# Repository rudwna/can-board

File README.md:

# MCP2515 + MCP2551 CAN development board

This board is for CAN bus development using MCP2515 CAN controller and MCP2551 CAN transceiver.
Created after experiences odd behaviors when using breadboard for development ([just like this](http://www.microchip.com/forums/m704332.aspx))

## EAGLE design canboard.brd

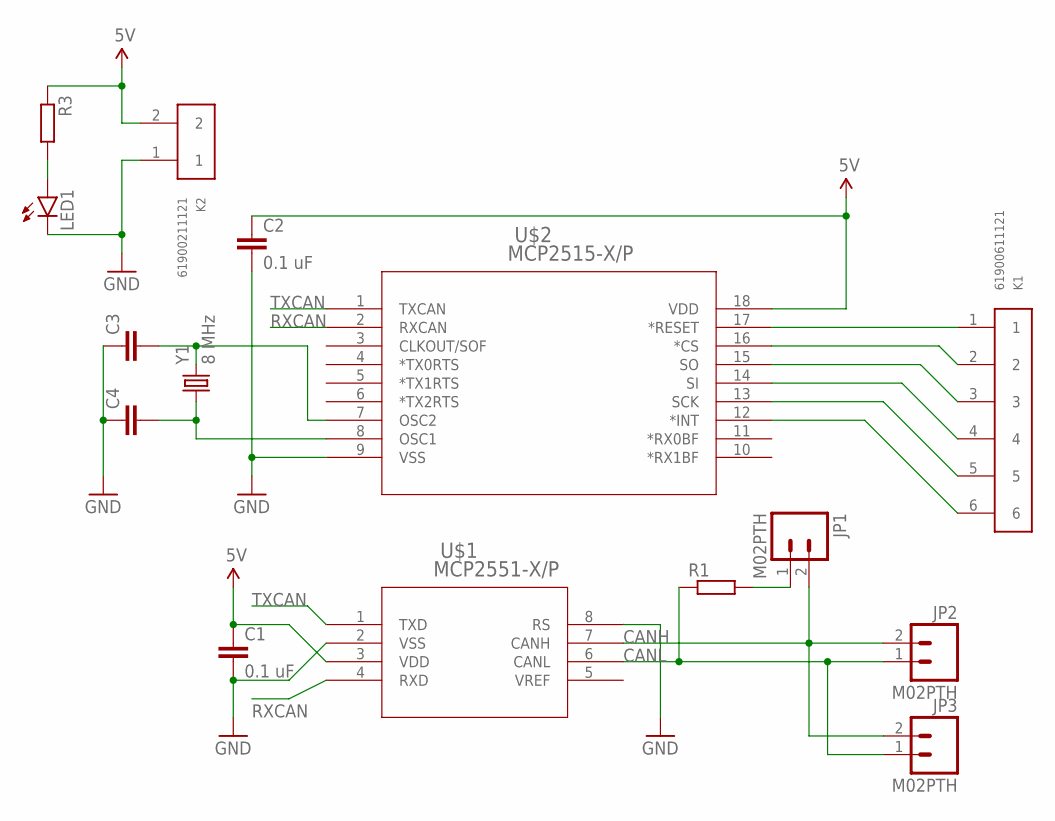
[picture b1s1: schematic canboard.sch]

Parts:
C1, C2: 0.1 uF; C050-030X075
C3, C4: C-EU025-025X050; C025-025X050
JP1, JP2, JP3: M02PTH; 1X02
K1: 61900611121
K2: 61900211121
LED1: LED3MM
R1, R3: R-EU_0207/10; 0207/10
U$1: MCP2551-X/P; PDIP8_300MC
U$2: MCP2515-X/P; PDIP18_300MC
Y1: 8 MHz; HC49US

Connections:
5V: C1.1, C2.1, K2.2, R3.1, U$1.3 (VDD), U$2.18 (VDD)
CANH: JP1.2, JP2.2, JP3.2, U$1.7 (CANH)
CANL: JP2.1, JP3.1, R1.1, U$1.6 (CANL)
GND: C1.2, C2.2, C3.1, C4.1, K2.1, LED1.K (C), U$1.2 (VSS), U$1.8 (RS), U$2.9 (VSS)
unnamed: C4.2, U$2.8 (OSC1), Y1.1
unnamed: C3.2, U$2.7 (OSC2), Y1.2
unnamed: K1.1, U$2.17 (*RESET)
unnamed: K1.2, U$2.16 (*CS)
unnamed: K1.3, U$2.15 (SO)
unnamed: K1.4, U$2.14 (SI)
unnamed: K1.5, U$2.13 (SCK)
unnamed: LED1.A, R3.2
unnamed: JP1.1, R1.2
unnamed: K1.6, U$2.12 (*INT)
RXCAN: U$1.4 (RXD), U$2.2 (RXCAN)
TXCAN: U$1.1 (TXD), U$2.1 (TXCAN)

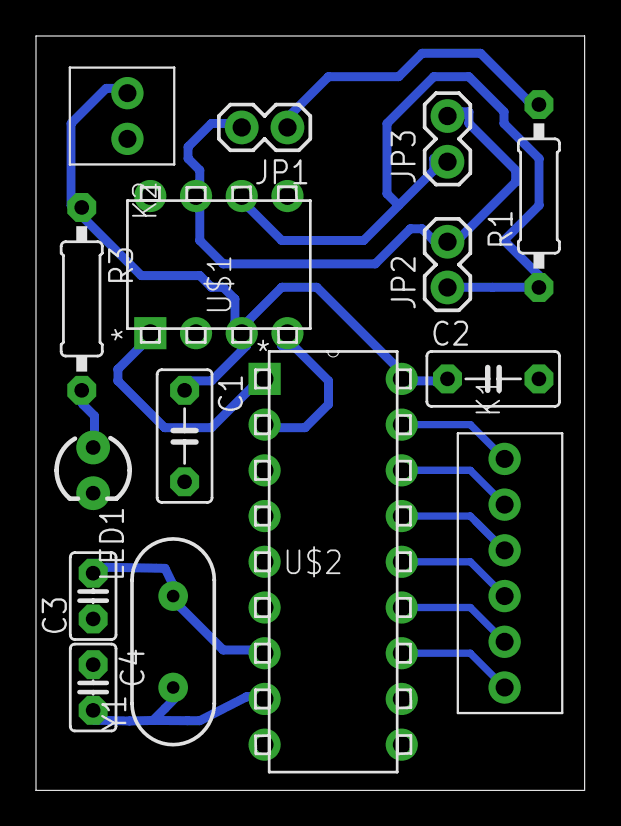
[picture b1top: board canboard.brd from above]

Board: 2 copper layers, 30.5 x 41.9 mm, 15 parts (0 on the bottom side), 16 nets.

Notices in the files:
parts and their libraries:
SparkFun-Connectors: Licensing: Creative Commons ShareAlike 4.0 International - https://creativecommons.org/licenses/by-sa/4.0
EagleLibrary_Wuerth_Elektronik _eiCan_Wi: Copyright: Würth Elektronik
